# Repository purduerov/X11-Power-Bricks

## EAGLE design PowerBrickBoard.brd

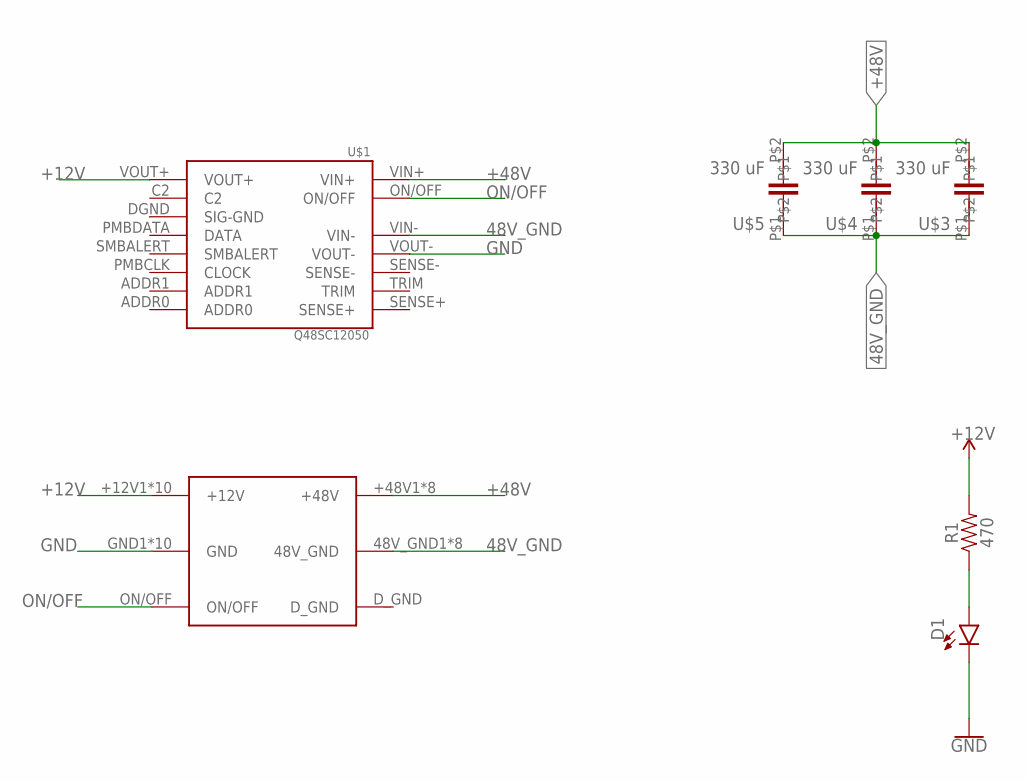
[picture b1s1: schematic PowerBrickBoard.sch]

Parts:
D1: LED0603; LED-0603
R1: 470; 0603
U$1: Q48SC12050
U$2: BRICK_TO_POWER_DIST_WHOLE
U$3, U$4, U$5: 330 uF; UCM1H331MNL1GS

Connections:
48V_GND: U$1.VIN-, U$2.48V_GND1 (48V_GND), U$2.48V_GND2 (48V_GND), U$2.48V_GND3 (48V_GND), U$2.48V_GND4 (48V_GND), U$2.48V_GND5 (48V_GND), U$2.48V_GND6 (48V_GND), U$2.48V_GND7 (48V_GND), U$2.48V_GND8 (48V_GND), U$3.P$1, U$4.P$1, U$5.P$1
+12V: R1.2, U$1.VOUT+, U$2.+12V1 (+12V), U$2.+12V2 (+12V), U$2.+12V3 (+12V), U$2.+12V4 (+12V), U$2.+12V5 (+12V), U$2.+12V6 (+12V), U$2.+12V7 (+12V), U$2.+12V8 (+12V), U$2.+12V9 (+12V), U$2.+12V10 (+12V)
+48V: U$1.VIN+, U$2.+48V1 (+48V), U$2.+48V2 (+48V), U$2.+48V3 (+48V), U$2.+48V4 (+48V), U$2.+48V5 (+48V), U$2.+48V6 (+48V), U$2.+48V7 (+48V), U$2.+48V8 (+48V), U$3.P$2, U$4.P$2, U$5.P$2
D_GND: U$1.DGND (SIG-GND)
GND: D1.C, U$1.VOUT-, U$2.GND1 (GND), U$2.GND2 (GND), U$2.GND3 (GND), U$2.GND4 (GND), U$2.GND5 (GND), U$2.GND6 (GND), U$2.GND7 (GND), U$2.GND8 (GND), U$2.GND9 (GND), U$2.GND10 (GND)
unnamed: D1.A, R1.1
ON/OFF: U$1.ON/OFF, U$2.ON/OFF

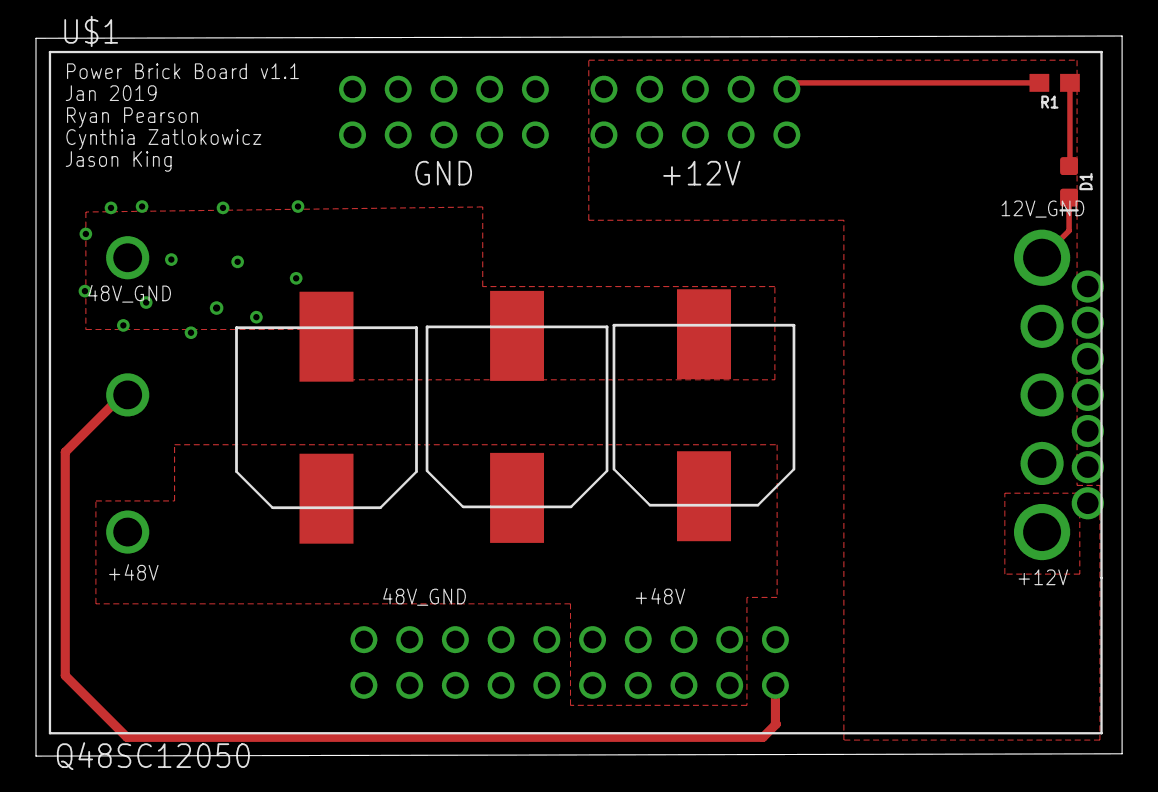
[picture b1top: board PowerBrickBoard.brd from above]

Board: 2 copper layers, 60.3 x 40.0 mm, 7 parts (1 on the bottom side), 6 nets.

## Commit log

2018-09-19 added gitignore
2018-11-09 added brick part in schematic and board with 1 brick
2018-11-10 added connectors
2018-11-10 fixed the connectors
2018-11-30 Routed board
2018-11-30 Updated d_gnd trace to be larger
2018-11-30 Widened polygons
2018-12-17 Added capacitors
2018-12-30 respositened capacitors
    fixed the board up
2018-12-30 added text
2018-12-30 forgot the date
2018-12-31 added LED
    added LED between 12V and GND
2019-01-03 added silkscreen
2019-01-12 fixed the silkscreen
    looks much better
2019-01-14 Increased trace width of polygons.. we need it
2019-02-05 rerouted the board
    had to update the part so i had to move things around and redo the routing/polygons
2019-02-05 Updated name, moved some things
    updated name to v1.1 and moved resistor and LED so the polygon for 12V was larger
2019-02-06 updated to jasons desires
    changed width sizes and corrected pin layout of on/off switch, added more vias for the overlapping polygon, moved resistor and LED to optimize the +12V polygon

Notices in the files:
parts and their libraries:
SparkFun-LED: Licensing: Creative Commons ShareAlike 4.0 International - https://creativecommons.org/licenses/by-sa/4.0
